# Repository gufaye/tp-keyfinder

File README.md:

# KeyFinder

A project developed as part of an electronic and software design course.

The goal was to fully design a connected keychain, from the mechanical enclosure and electronic PCB to the embedded firmware.

## Overview

The project includes:

* Mechanical design of the enclosure and keychain using Fusion 360
* Electronic schematic and PCB design using KiCad
* Development of a Bluetooth Low Energy (BLE) firmware using Zephyr
* Control of a physical button and multiple LEDs
* Communication with a Bluetooth device

The mechanical model was designed manually from scratch during the course.

## Prototype Features

The current firmware provides the following features:

* Automatically blink an LED
* Control an LED using a physical button
* Control an LED remotely via Bluetooth
* Establish a Bluetooth Low Energy connection
* Simulate a battery measurement
* Resume Bluetooth advertising after disconnection

## Repository Structure

```text
hardware/
├── KeyFinder.kicad_sch
├── nrf52832_qfax.kicad_sch
├── nrf52832_qfax.kicad_pcb
├── nrf52832_qfax.kicad_pro
└── nrf52832_qfax-backups/

software/
├── peripheral_hr_button/
│   ├── src/
│   │   └── main.c
│   ├── boards/
│   ├── prj.conf
│   ├── CMakeLists.txt
│   └── README.rst
└── Projet fusion/
    └── Fusion 360 mechanical model
```

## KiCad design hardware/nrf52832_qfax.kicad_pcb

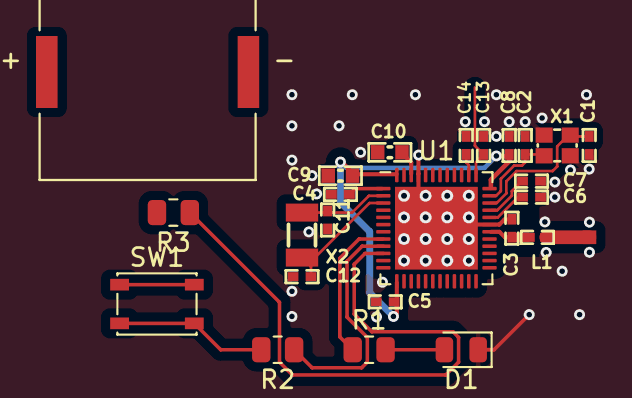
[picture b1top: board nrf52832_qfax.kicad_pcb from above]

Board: 2 copper layers, 24 parts (0 on the bottom side), 13 nets.

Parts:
BZ1: Buzzer; SPKR_PKLCS1212E4001-R1
C1, C2: 12pF; CAPC1005X04L
C3: 0.8pF; CAPC1005X04L
C4, C5, C8: 100nF; CAPC1005X04L
C6: N.C.; CAPC1005X04L
C7: 100pF; CAPC1005X04L
C9: 4.7µF; CAPC1608X06L
C10: 1.0µF; CAPC1608X06L
C11, C12: 12pF; _Repositories_Applications_test_rsk_lib_RSK-ONLY_PcbLib_Pas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
C13, C14: 12pF; _Applications_repo_test_rsk_lib_RSK-ONLY_PcbLib_Passive.Pcb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
D1: LED; LED_0805_2012Metric
L1: 3.9nH; INDC1005X04L
R1, R2, R3: R; R_0805_2012Metric
SW1: SW_Push; SW_SPST_PTS810
U1: nRF52832-QFAA; QFN-48-1EP_6x6mm_P0.4mm_EP4.6x4.6mm
X1: 32MHz; BT-XTAL_2016
X2: 32.768kHz; _Repositories_Applications_test_rsk_lib_RSK-ONLY_PcbLib_pcb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

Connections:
/BZ1: R3.1, U1.10 (P0.08)
/LED0: R1.1, U1.8 (P0.06)
/P0.07: R2.1, U1.9 (P0.07)
GND: C1.2, C2.2, C3.1, C4.2, C5.2, C6.1, C7.2, C8.2, C9.2, C10.1, C11.2, C12.2, C13.2, C14.2, D1.1 (K), U1.31 (VSS), U1.45 (VSS), X1.2, X1.4
unnamed: D1.2 (A), R1.2
unnamed: R2.2, SW1.2
NetC3_2: C3.2, L1.1
P0.00/XL1: C11.1, X2.1
P0.01/XL2: C12.1, X2.2
VDD_NRF: C5.1, C8.1, C9.1
VDD_nRF: U1.13 (VDD), U1.36 (VDD), U1.48 (VDD)
XC1: C1.1, X1.1
XC2: C2.1, X1.3
